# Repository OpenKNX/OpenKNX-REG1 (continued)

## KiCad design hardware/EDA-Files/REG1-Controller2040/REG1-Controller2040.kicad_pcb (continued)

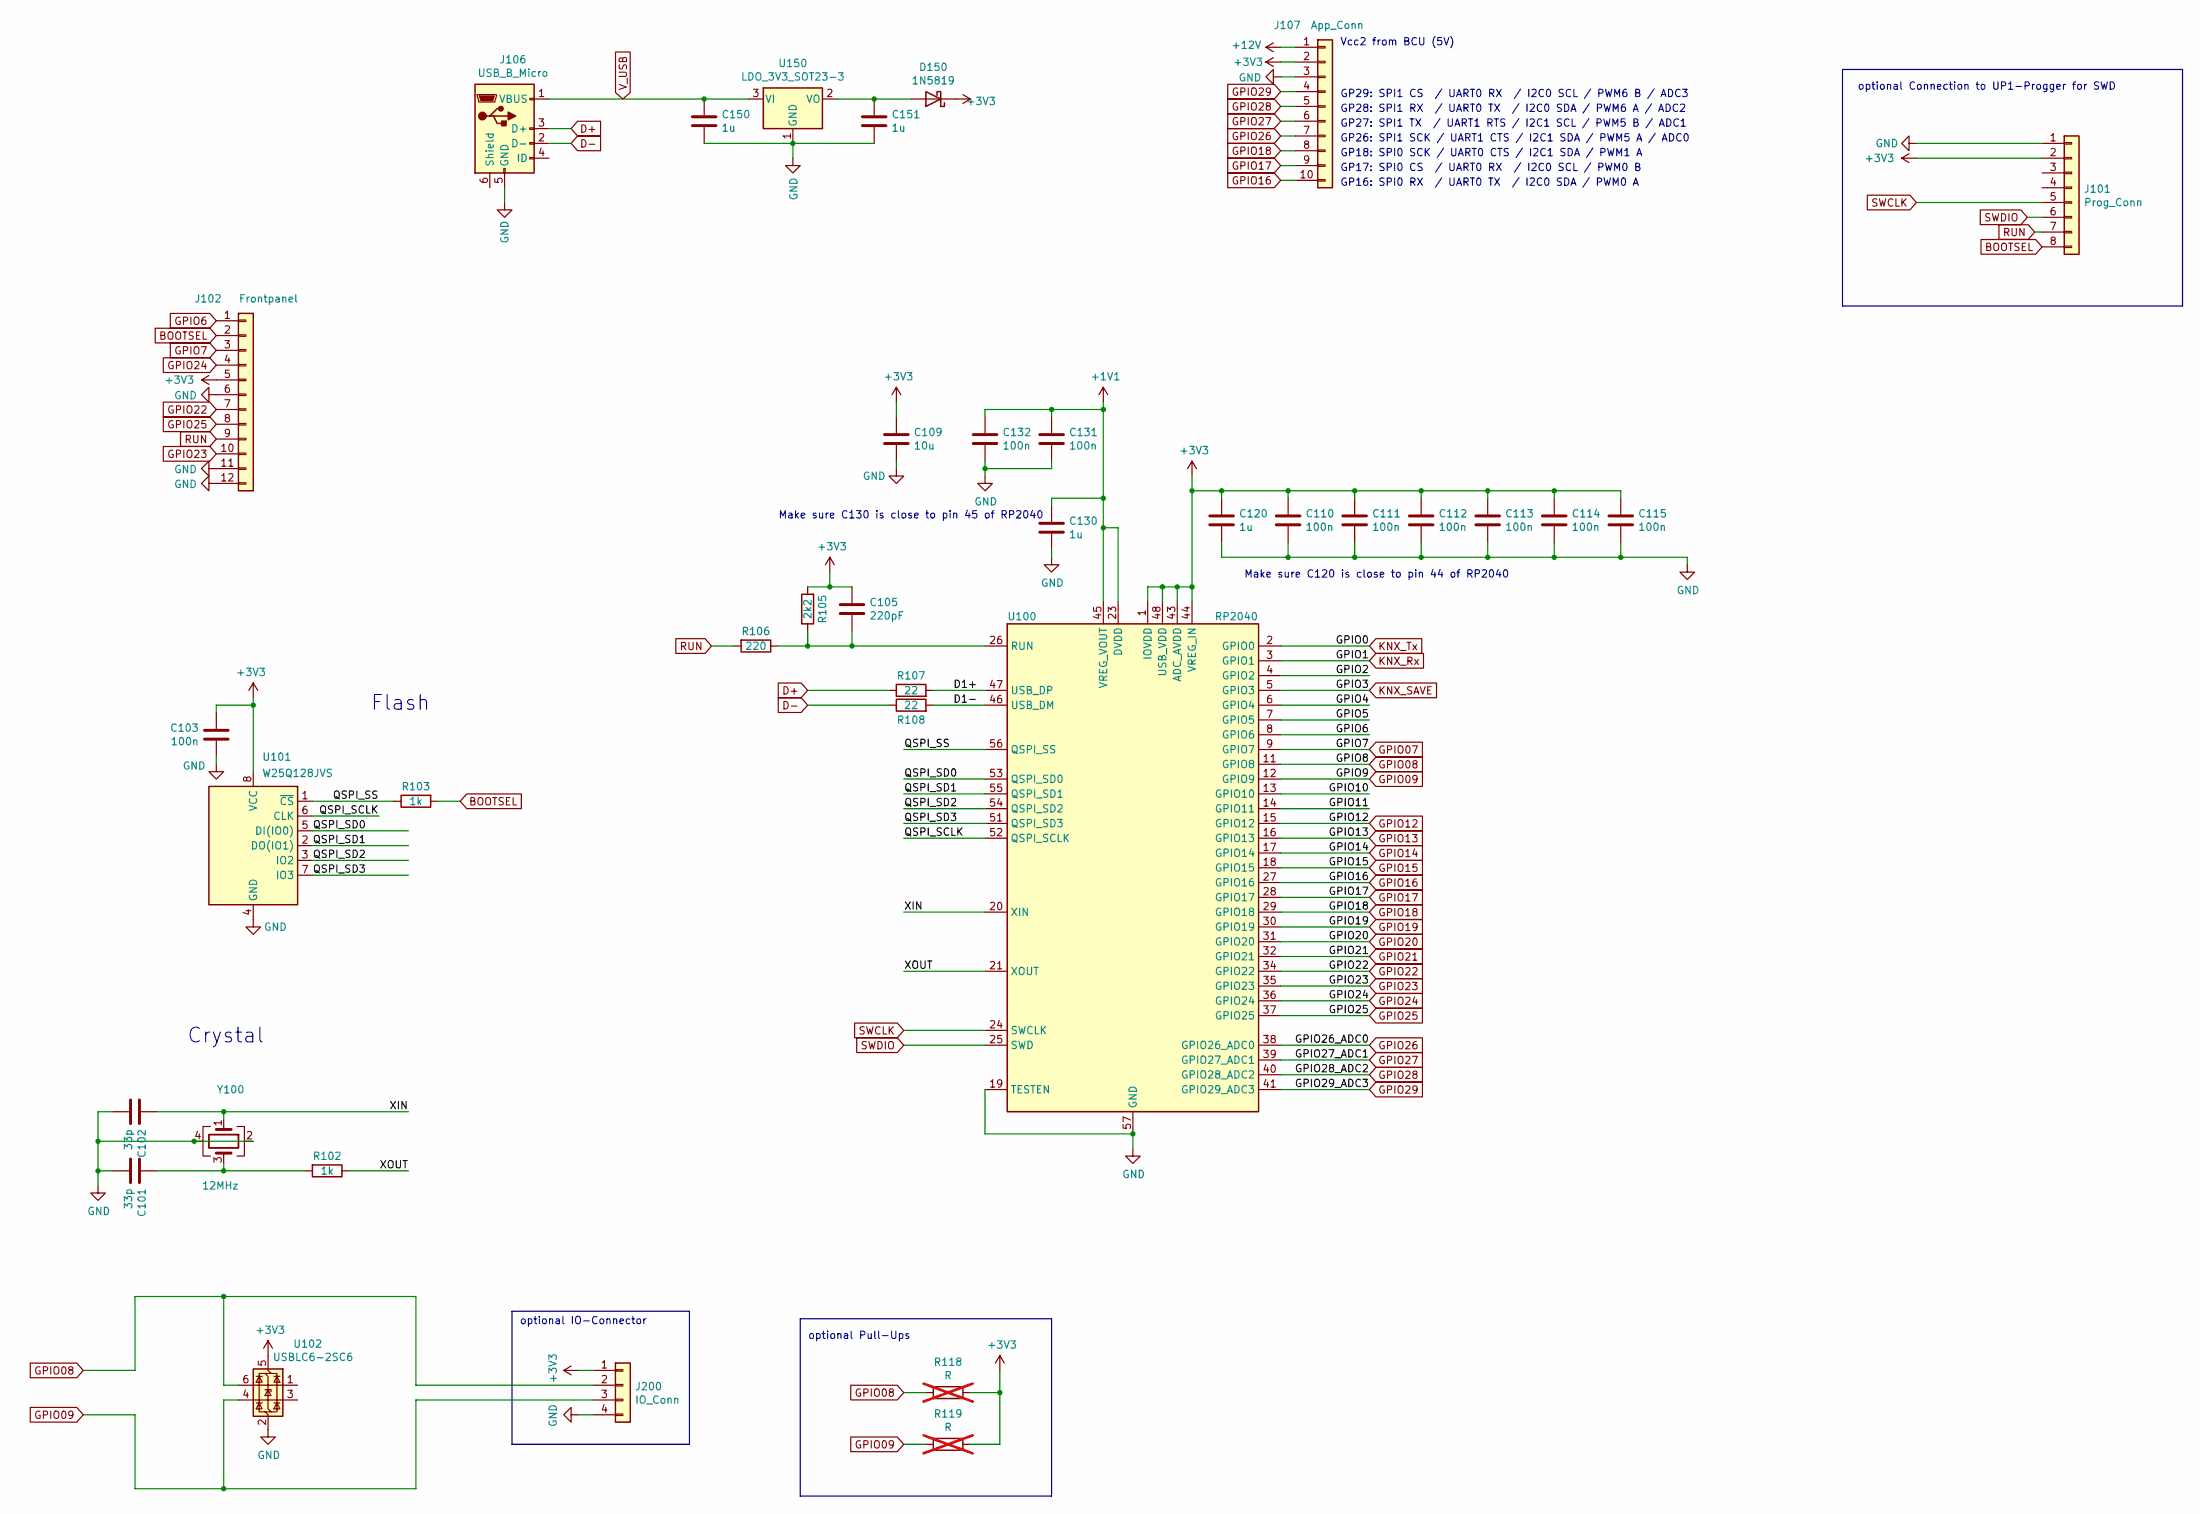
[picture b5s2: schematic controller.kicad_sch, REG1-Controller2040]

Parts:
C101, C102: 33p; C_0402_1005Metric
C103, C110, C111, C112, C113, C114, C115, C131, C132: 100n; C_0402_1005Metric
C105: 220pF; C_0402_1005Metric
C109: 10u; C_0805_2012Metric
C120, C130, C150, C151: 1u; C_0402_1005Metric
D150: 1N5819; D_SOD-323
J101: Prog_Conn; CONN-TH_1.25-8AW_reversed
J102: Frontpanel; CONN-TH-10P_AFC11-S10ICC-00
J106: USB_B_Micro; USB_Micro-B_JING_C10418
J107: App_Conn; PinHeader_1x10_P2.54mm_Vertical
J200: IO_Conn; PhoenixContact_MC_1,5_4-G-3.5_1x04_P3.50mm_Horizontal
R102, R103: 1k; R_0402_1005Metric
R105: 2k2; R_0402_1005Metric
R106: 220; R_0402_1005Metric
R107, R108: 22; R_0402_1005Metric
R118, R119: R; R_0805_2012Metric_Pad1.20x1.40mm_HandSolder; not fitted
U100: RP2040; RP2040-QFN-56_noThermalVias
U101: W25Q128JVS; SOIC-8_5.23x5.23mm_P1.27mm
U102: USBLC6-2SC6; SOT-23-6
U150: LDO_3V3_SOT23-3; SOT-23
Y100: 12MHz; Crystal_SMD_3225-4Pin_3.2x2.5mm

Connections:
+1V1: C130.1, C131.1, C132.1, U100.23 (DVDD), U100.45 (VREG_VOUT), U100.50 (DVDD)
+3V3: C103.1, C105.1, C109.1, C110.1, C111.1, C112.1, C113.1, C114.1, C115.1, C120.1, D150.1 (K), J101.2, J107.2, J200.1, R105.2, R118.1, R119.1, U100.1 (IOVDD), U100.10 (IOVDD), U100.22 (IOVDD), U100.33 (IOVDD), U100.42 (IOVDD), U100.43 (ADC_AVDD), U100.44 (VREG_IN), U100.48 (USB_VDD), U100.49 (IOVDD), U101.8 (VCC), U102.5 (VBUS); also elsewhere on the board
+12V: J107.1; also elsewhere on the board
/Controller/D1+: R107.2, U100.47 (USB_DP)
/Controller/D1-: R108.2, U100.46 (USB_DM)
/Controller/GPIO2: U100.4 (GPIO2)
/Controller/GPIO4: U100.6 (GPIO4)
/Controller/GPIO5: U100.7 (GPIO5)
/Controller/GPIO10: U100.13 (GPIO10)
/Controller/GPIO11: U100.14 (GPIO11)
/Controller/QSPI_SCLK: U100.52 (QSPI_SCLK), U101.6 (CLK)
/Controller/QSPI_SD0: U100.53 (QSPI_SD0), U101.5 (DI(IO0))
/Controller/QSPI_SD1: U100.55 (QSPI_SD1), U101.2 (DO(IO1))
/Controller/QSPI_SD2: U100.54 (QSPI_SD2), U101.3 (IO2)
/Controller/QSPI_SD3: U100.51 (QSPI_SD3), U101.7 (IO3)
/Controller/QSPI_SS: R103.1, U100.56 (QSPI_SS), U101.1 (~CS)
/Controller/XIN: C102.1, U100.20 (XIN), Y100.1
/Controller/XOUT: R102.1, U100.21 (XOUT)
BOOTSEL: J101.8, R103.2; also elsewhere on the board
D+: J106.3 (D+), R107.1
D-: J106.2 (D-), R108.1
GND: C101.2, C102.2, C103.2, C109.2, C110.2, C111.2, C112.2, C113.2, C114.2, C115.2, C120.2, C130.2, C131.2, C132.2, C150.2, C151.2, J101.1, J106.5 (GND), J107.3, J200.4, U100.19 (TESTEN), U100.57 (GND), U101.4 (GND), U102.2 (GND), U150.1 (GND), Y100.2, Y100.4; also elsewhere on the board
GPIO6: U100.8 (GPIO6); also elsewhere on the board
GPIO07: U100.9 (GPIO7); also elsewhere on the board
GPIO08: J200.2, R118.2, U100.11 (GPIO8), U102.6 (I/O1)
GPIO09: J200.3, R119.2, U100.12 (GPIO9), U102.4 (I/O2)
GPIO12: U100.15 (GPIO12)
GPIO13: U100.16 (GPIO13)
GPIO14: U100.17 (GPIO14)
GPIO15: U100.18 (GPIO15)
GPIO16: J107.10, U100.27 (GPIO16)
GPIO17: J107.9, U100.28 (GPIO17)
GPIO18: J107.8, U100.29 (GPIO18)
GPIO19: U100.30 (GPIO19)
GPIO20: U100.31 (GPIO20)
GPIO21: U100.32 (GPIO21)
GPIO22: U100.34 (GPIO22); also elsewhere on the board
GPIO23: U100.35 (GPIO23); also elsewhere on the board
GPIO24: U100.36 (GPIO24); also elsewhere on the board
GPIO25: U100.37 (GPIO25); also elsewhere on the board
GPIO26: J107.7, U100.38 (GPIO26_ADC0)
GPIO27: J107.6, U100.39 (GPIO27_ADC1)
GPIO28: J107.5, U100.40 (GPIO28_ADC2)
GPIO29: J107.4, U100.41 (GPIO29_ADC3)
KNX_Rx: U100.3 (GPIO1); also elsewhere on the board
KNX_SAVE: U100.5 (GPIO3); also elsewhere on the board
KNX_Tx: U100.2 (GPIO0); also elsewhere on the board
unnamed: C101.1, R102.2, Y100.3
unnamed: C151.1, D150.2 (A), U150.2 (VO)
unnamed: C105.2, R105.1, R106.1, U100.26 (RUN)
RUN: J101.7, R106.2; also elsewhere on the board
SWCLK: J101.5, U100.24 (SWCLK)
SWDIO: J101.6, U100.25 (SWD)
V_USB: C150.1, J106.1 (VBUS), U150.3 (VI)

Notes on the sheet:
GP18: SPI0 SCK / UART0 CTS / I2C1 SDA / PWM1 A
GP16: SPI0 RX / UART0 TX / I2C0 SDA / PWM0 A
optional Connection to UP1-Progger for SWD
Make sure C130 is close to pin 45 of RP2040
GP17: SPI0 CS / UART0 RX / I2C0 SCL / PWM0 B
Vcc2 from BCU (5V)
GP29: SPI1 CS / UART0 RX / I2C0 SCL / PWM6 B / ADC3
Flash
GP28: SPI1 RX / UART0 TX / I2C0 SDA / PWM6 A / ADC2
GP26: SPI1 SCK / UART1 CTS / I2C1 SDA / PWM5 A / ADC0
optional Pull-Ups
Crystal
GP27: SPI1 TX / UART1 RTS / I2C1 SCL / PWM5 B / ADC1
optional IO-Connector
Make sure C120 is close to pin 44 of RP2040

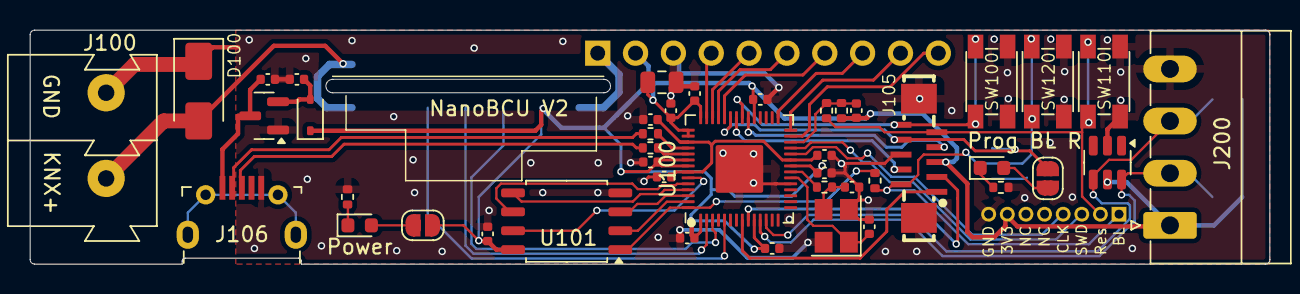
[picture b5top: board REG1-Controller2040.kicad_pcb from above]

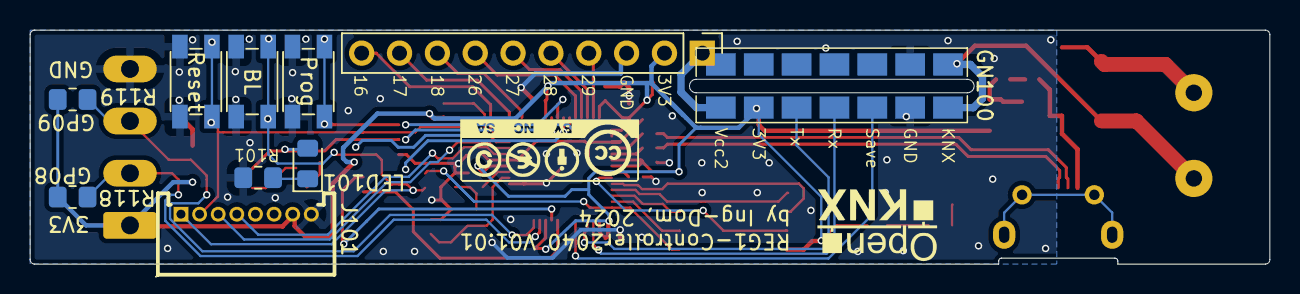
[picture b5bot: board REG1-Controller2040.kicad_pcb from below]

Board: 2 copper layers, 83.2 x 15.7 mm, 55 parts (12 on the bottom side), 48 nets.

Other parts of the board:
G1: LOGO; CC-BY-NY-SA_12x4
G2: LOGO; OpenKNX_Logo_10x10
J105: Frontpanel; CONN-TH-10P_AFC11-S10ICC-00

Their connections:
+3V3: J105.5; also elsewhere on the board
BOOTSEL: J105.2; also elsewhere on the board
GND: J105.6, J105.11, J105.12; also elsewhere on the board
GPIO6: J105.1; also elsewhere on the board
GPIO07: J105.3; also elsewhere on the board
GPIO22: J105.7; also elsewhere on the board
GPIO23: J105.10; also elsewhere on the board
GPIO24: J105.4; also elsewhere on the board
GPIO25: J105.8; also elsewhere on the board
RUN: J105.9; also elsewhere on the board

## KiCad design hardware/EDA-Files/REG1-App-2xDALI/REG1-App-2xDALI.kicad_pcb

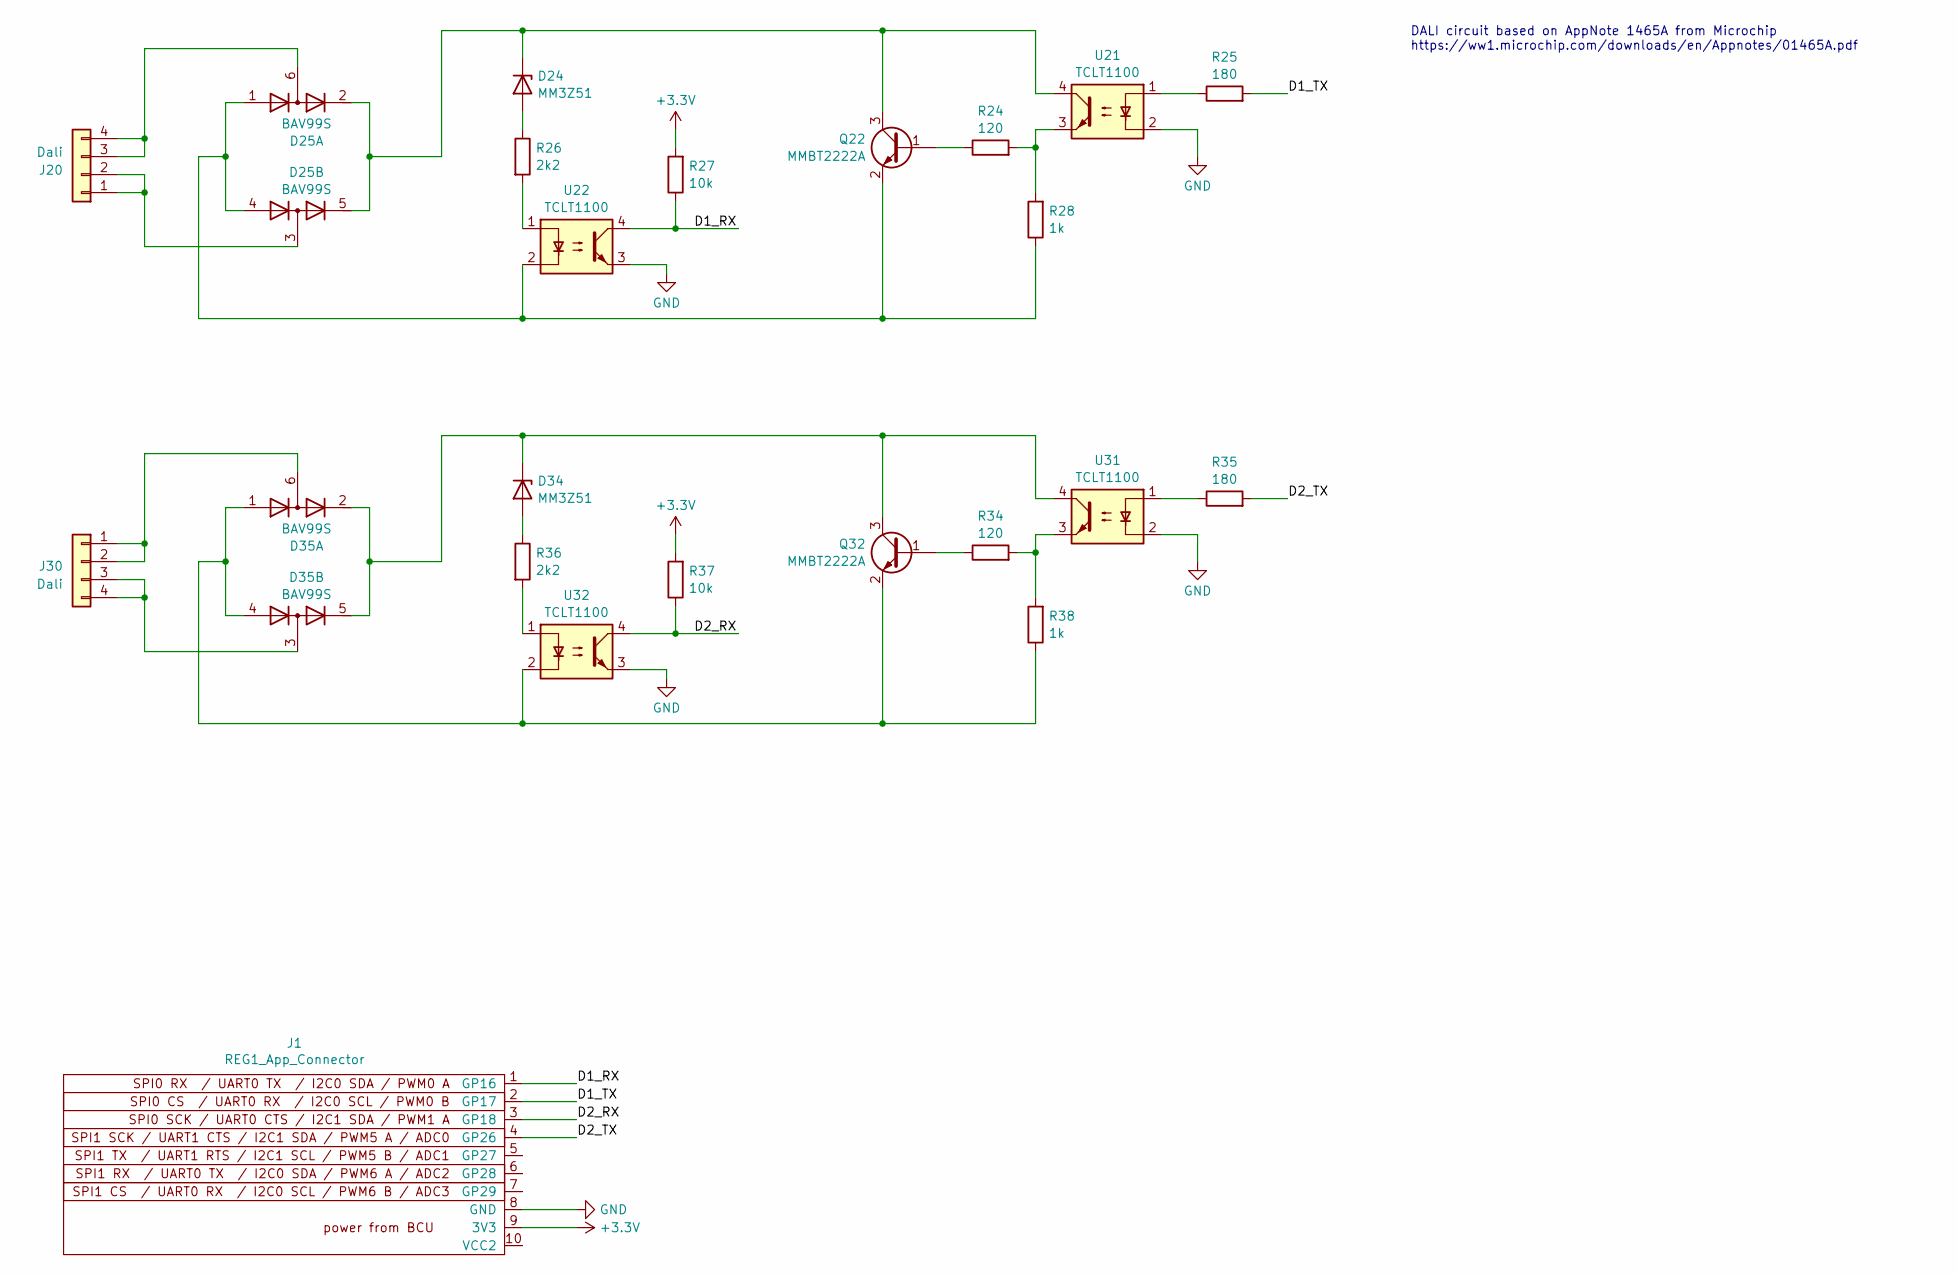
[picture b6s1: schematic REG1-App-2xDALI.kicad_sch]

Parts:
D24, D34: MM3Z51; D_SOD-323F
D25, D35: BAV99S; SOT-363_SC-70-6
J1: REG1_App_Connector; PinHeader_1x10_P2.54mm_Horizontal
J20, J30: Dali; PhoenixContact_MC_1,5_4-G-3.5_1x04_P3.50mm_Horizontal
Q22, Q32: MMBT2222A; SOT-23
R24, R34: 120; R_0603_1608Metric
R25, R35: 180; R_0603_1608Metric
R26, R36: 2k2; R_0603_1608Metric
R27, R37: 10k; R_0603_1608Metric
R28, R38: 1k; R_0603_1608Metric
U21, U22, U31, U32: TCLT1100; SOP-4_7.5x4.1mm_P2.54mm

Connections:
+3.3V: J1.9 (3V3), R27.2, R37.2
/D1_RX: J1.1 (GP16), R27.1, U22.4
/D1_TX: J1.2 (GP17), R25.2
/D2_RX: J1.3 (GP18), R37.1, U32.4
/D2_TX: J1.4 (GP26), R35.2
GND: J1.8 (GND), U21.2, U22.3, U31.2, U32.3
unnamed: D24.2 (A), R26.1
unnamed: D24.1 (K), D25.2 (K2), D25.5 (K4), Q22.3 (C), U21.4
unnamed: D25.1 (A1), D25.4 (A3), Q22.2 (E), R28.1, U22.2
unnamed: D25.6 (K3A4), J20.3, J20.4
unnamed: D25.3 (K1A2), J20.1, J20.2
unnamed: D34.2 (A), R36.1
unnamed: D34.1 (K), D35.2 (K2), D35.5 (K4), Q32.3 (C), U31.4
unnamed: D35.1 (A1), D35.4 (A3), Q32.2 (E), R38.1, U32.2
unnamed: D35.6 (K3A4), J30.1, J30.2
unnamed: D35.3 (K1A2), J30.3, J30.4
unnamed: Q22.1 (B), R24.1
unnamed: Q32.1 (B), R34.1
unnamed: R24.2, R28.2, U21.3
unnamed: R25.1, U21.1
unnamed: R26.2, U22.1
unnamed: R34.2, R38.2, U31.3
unnamed: R35.1, U31.1
unnamed: R36.2, U32.1

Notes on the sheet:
DALI circuit based on AppNote 1465A from Microchip https://ww1.microchip.com/downloads/en/Appnotes/01465A.pdf

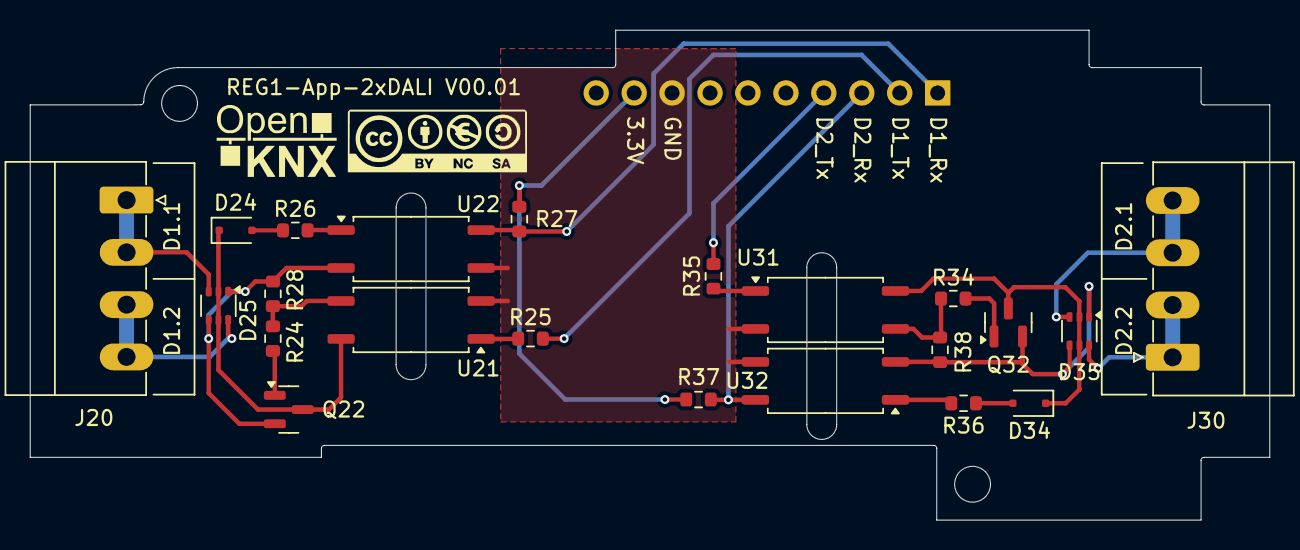
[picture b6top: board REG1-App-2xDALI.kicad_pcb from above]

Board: 2 copper layers, 83.0 x 32.8 mm, 25 parts (1 on the bottom side), 24 nets.

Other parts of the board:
G1: LOGO; CC-BY-NY-SA_12x4
G2: LOGO; OpenKNX_Logo_10x10

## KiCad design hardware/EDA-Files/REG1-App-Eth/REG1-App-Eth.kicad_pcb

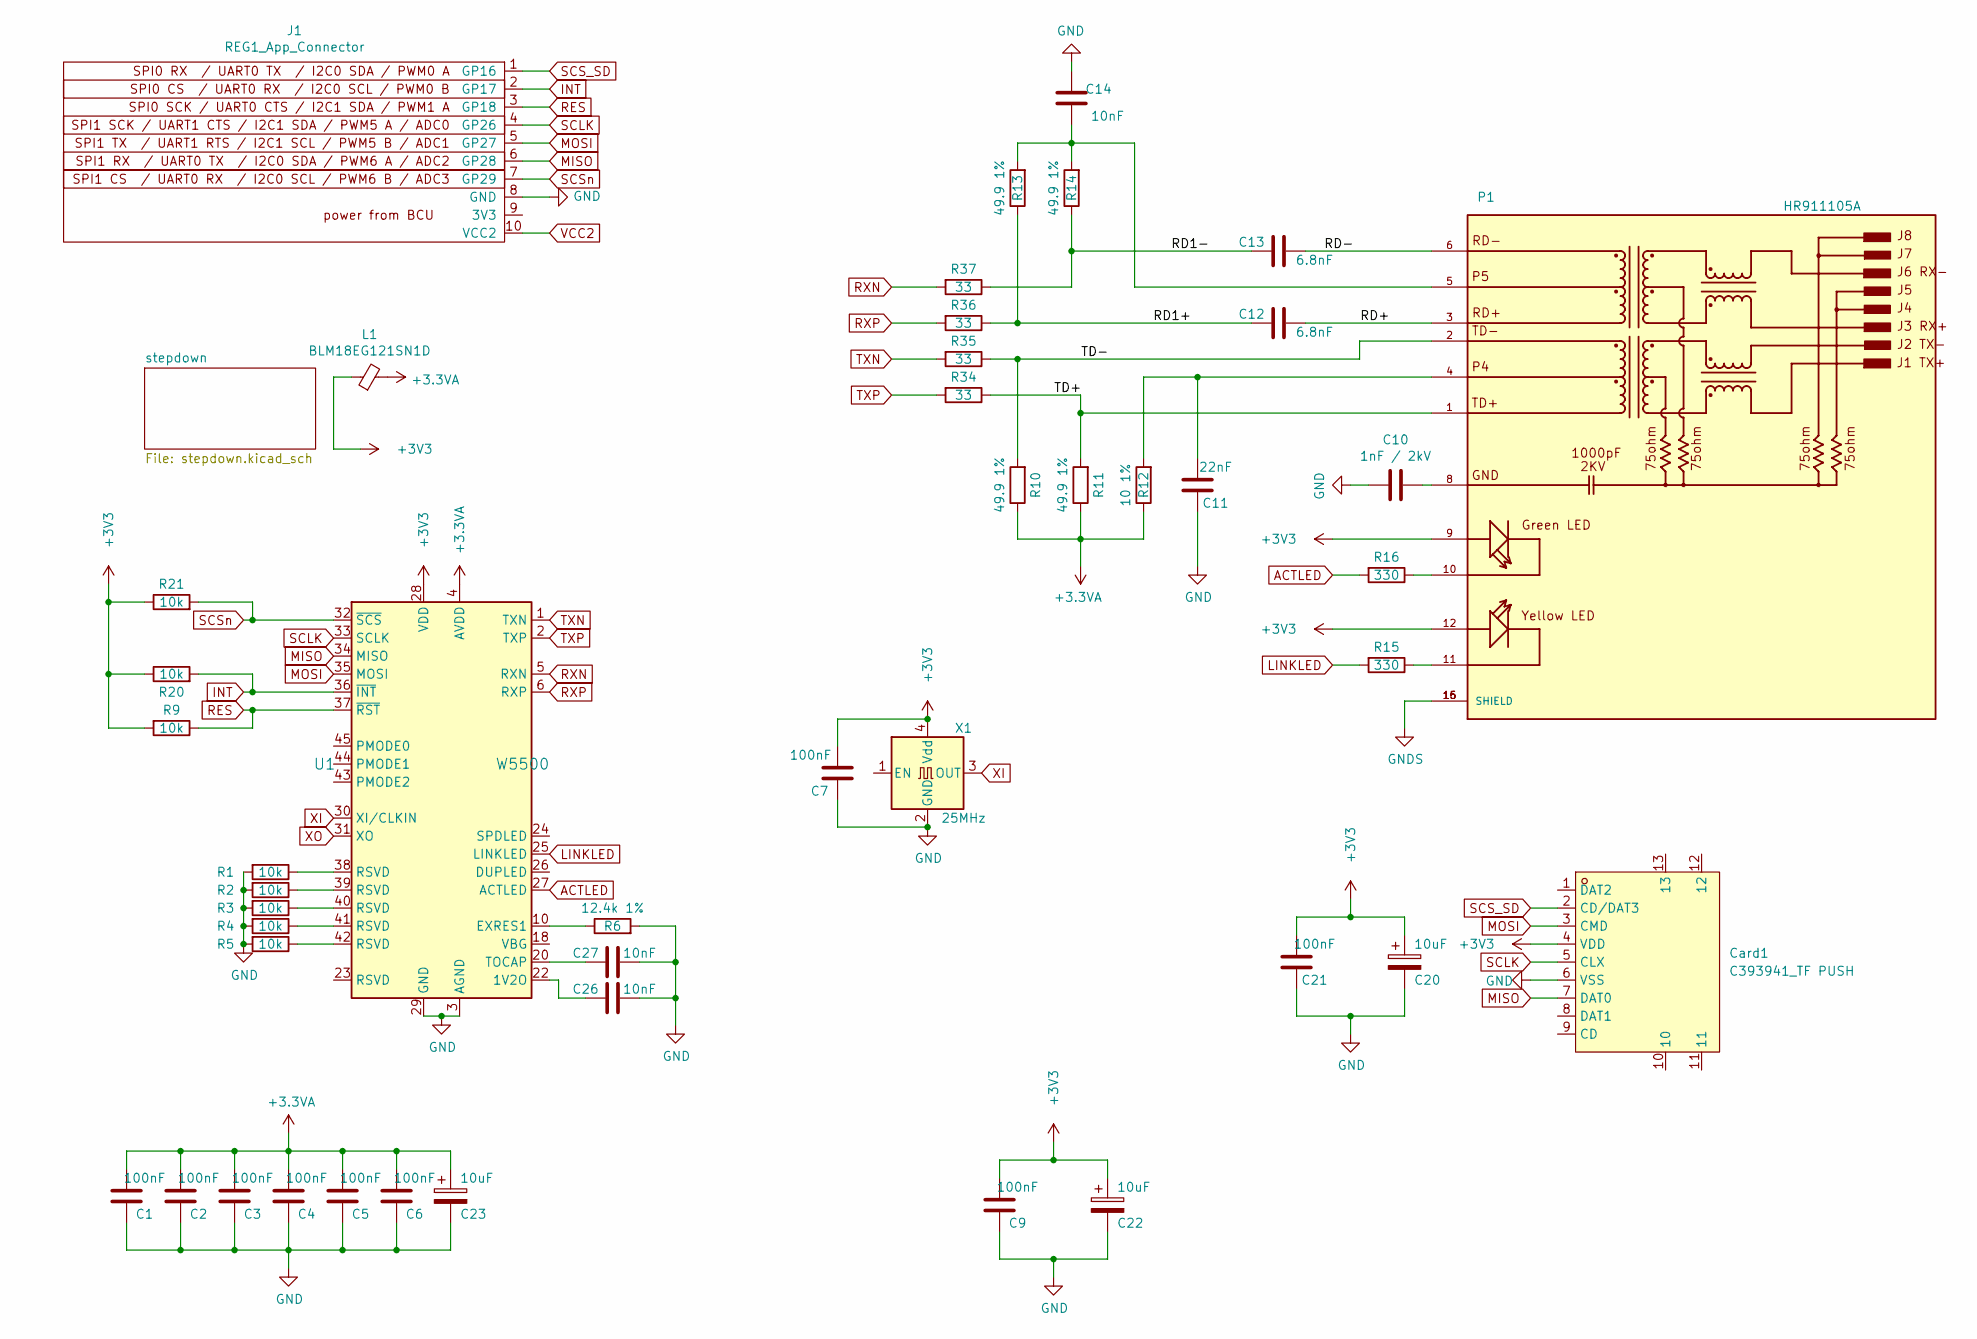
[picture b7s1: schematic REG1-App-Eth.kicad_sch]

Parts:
C1, C2, C3, C4, C5, C6, C7, C9, C21: 100nF; C_0402_1005Metric
C10: 1nF / 2kV; C_1206_3216Metric
C11: 22nF; C_0402_1005Metric
C12, C13: 6.8nF; C_0402_1005Metric
C14, C26, C27: 10nF; C_0402_1005Metric
C20, C22, C23: 10uF; CP_EIA-3216-18_Kemet-A
Card1: C393941_TF PUSH; C393941_TF-SMD_TF-PUSH_Handsolder
J1: REG1_App_Connector; PinHeader_1x10_P2.54mm_Horizontal
L1: BLM18EG121SN1D; L_0603_1608Metric
P1: HR911105A; HANRUN_HR911105A; PARTREV A
R1, R2, R3, R4, R5, R9, R20, R21: 10k; R_0402_1005Metric
R6: 12.4k 1%; R_0402_1005Metric
R10, R11, R13, R14: 49.9 1%; R_0402_1005Metric
R12: 10 1%; R_0402_1005Metric
R15, R16: 330; R_0402_1005Metric
R34, R35, R36, R37: 33; R_0402_1005Metric
U1: W5500; LQFP-48_7x7mm_P0.5mm; MPN W5500; Digi-Key_PN 1278-1021-ND
X1: 25MHz; Crystal_SMD_3225-4Pin_3.2x2.5mm

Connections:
+3.3VA: C1.1, C2.1, C3.1, C4.1, C5.1, C6.1, C23.1, L1.2, R10.1, R11.1, R12.1, U1.4 (AVDD), U1.8 (AVDD), U1.11 (AVDD), U1.15 (AVDD), U1.17 (AVDD), U1.21 (AVDD)
+3V3: C7.1, C9.1, C20.1, C21.1, C22.1, Card1.4 (VDD), L1.1, P1.9, P1.12, R9.2, R20.1, R21.1, U1.28 (VDD), X1.4 (Vdd); also elsewhere on the board
/RD1+: C12.2, R13.1, R36.1
/RD1-: C13.2, R14.1, R37.1
/RD+: C12.1, P1.3
/RD-: C13.1, P1.6
/TD+: P1.1, R11.2, R34.1
/TD-: P1.2, R10.2, R35.1
ACTLED: R16.2, U1.27 (ACTLED)
GND: C1.2, C2.2, C3.2, C4.2, C5.2, C6.2, C7.2, C9.2, C10.2, C11.2, C14.2, C20.2, C21.2, C22.2, C23.2, C26.1, C27.2, Card1.6 (VSS), J1.8 (GND), R1.2, R2.2, R3.2, R4.2, R5.2, R6.2, U1.3 (AGND), U1.9 (AGND), U1.14 (AGND), U1.16 (AGND), U1.19 (AGND), U1.29 (GND), U1.48 (AGND), X1.2 (GND); also elsewhere on the board
GNDS: P1.15 (SHIELD), P1.16 (SHIELD)
INT: J1.2 (GP17), R20.2, U1.36 (~INT)
LINKLED: R15.2, U1.25 (LINKLED)
MISO: Card1.7 (DAT0), J1.6 (GP28), U1.34 (MISO)
MOSI: Card1.3 (CMD), J1.5 (GP27), U1.35 (MOSI)
unnamed: C10.1, P1.8
unnamed: C11.1, P1.4, R12.2
unnamed: C14.1, P1.5, R13.2, R14.2
unnamed: P1.10, R16.1
unnamed: P1.11, R15.1
unnamed: R1.1, U1.38 (RSVD)
unnamed: R2.1, U1.39 (RSVD)
unnamed: R3.1, U1.40 (RSVD)
unnamed: R4.1, U1.41 (RSVD)
unnamed: R5.1, U1.42 (RSVD)
unnamed: C26.2, U1.22 (1V2O)
unnamed: R6.1, U1.10 (EXRES1)
unnamed: C27.1, U1.20 (TOCAP)
RES: J1.3 (GP18), R9.1, U1.37 (~RST)
RXN: R37.2, U1.5 (RXN)
RXP: R36.2, U1.6 (RXP)
SCLK: Card1.5 (CLX), J1.4 (GP26), U1.33 (SCLK)
SCS_SD: Card1.2 (CD/DAT3), J1.1 (GP16)
SCSn: J1.7 (GP29), R21.2, U1.32 (~SCS)
TXN: R35.2, U1.1 (TXN)
TXP: R34.2, U1.2 (TXP)
VCC2: J1.10 (VCC2); also elsewhere on the board
XI: U1.30 (XI/CLKIN), X1.3 (OUT)
XO: U1.31 (XO)

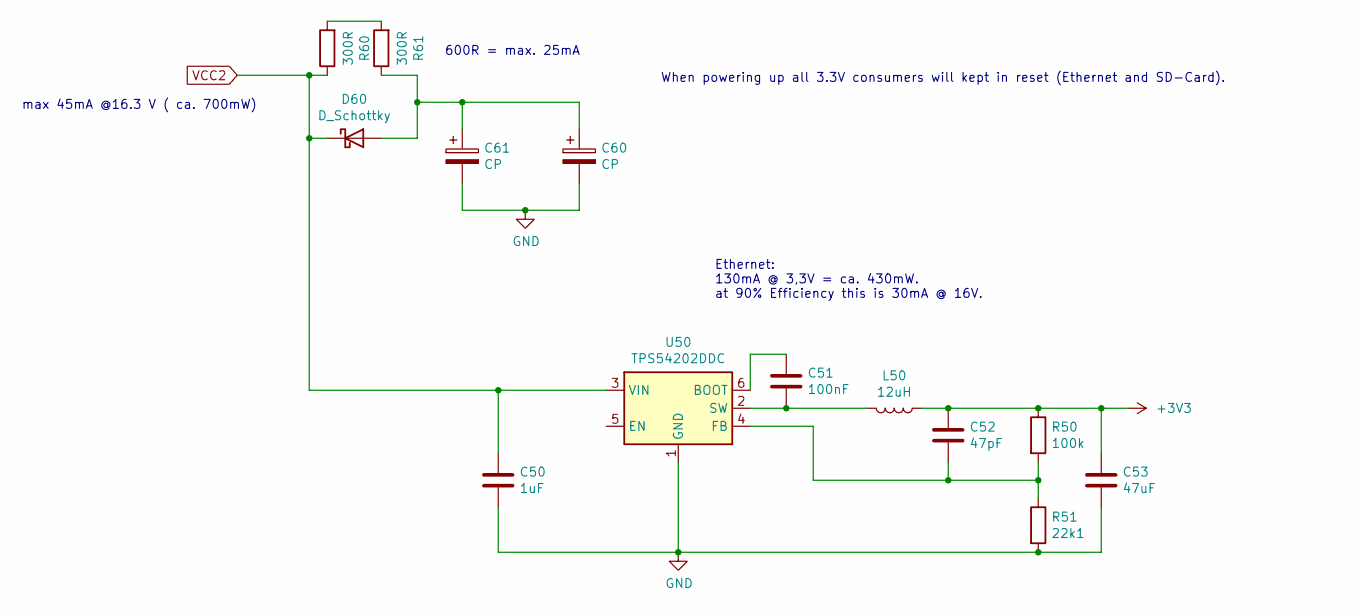
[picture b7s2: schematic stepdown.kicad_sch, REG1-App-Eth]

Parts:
C50: 1uF; C_0805_2012Metric
C51: 100nF; C_0603_1608Metric
C52: 47pF; C_0603_1608Metric
C53: 47uF; C_1206_3216Metric
C60, C61: CP; CP_Radial_D10.0mm_H20.0mm_P5.00mm_Horizontal
D60: D_Schottky; D_SOD-323
L50: 12uH; C96886_IND-SMD_L4.0-W4.0_Handsolder
R50: 100k; R_0603_1608Metric
R51: 22k1; R_0603_1608Metric
R60, R61: 300R; R_1206_3216Metric
U50: TPS54202DDC; SOT-23-6_Handsoldering

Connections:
+3V3: C52.1, C53.1, L50.1, R50.1; also elsewhere on the board
GND: C50.2, C53.2, C60.2, C61.2, R51.2, U50.1 (GND); also elsewhere on the board
unnamed: C60.1, C61.1, D60.2 (A), R61.1
unnamed: R60.2, R61.2
unnamed: C51.1, U50.6 (BOOT)
unnamed: C52.2, R50.2, R51.1, U50.4 (FB)
unnamed: C51.2, L50.2, U50.2 (SW)
VCC2: C50.1, D60.1 (K), R60.1, U50.3 (VIN); also elsewhere on the board

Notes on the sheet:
max 45mA @16.3 V ( ca. 700mW)
Ethernet: 130mA @ 3,3V = ca. 430mW. at 90% Efficiency this is 30mA @ 16V.
When powering up all 3.3V consumers will kept in reset (Ethernet and SD-Card).
600R = max. 25mA

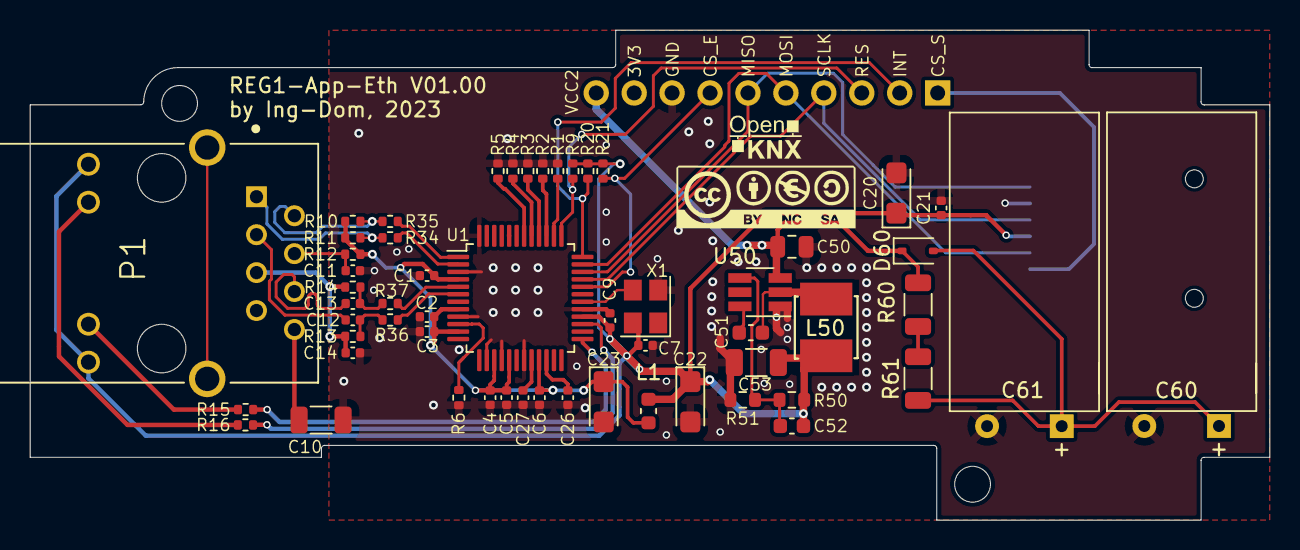
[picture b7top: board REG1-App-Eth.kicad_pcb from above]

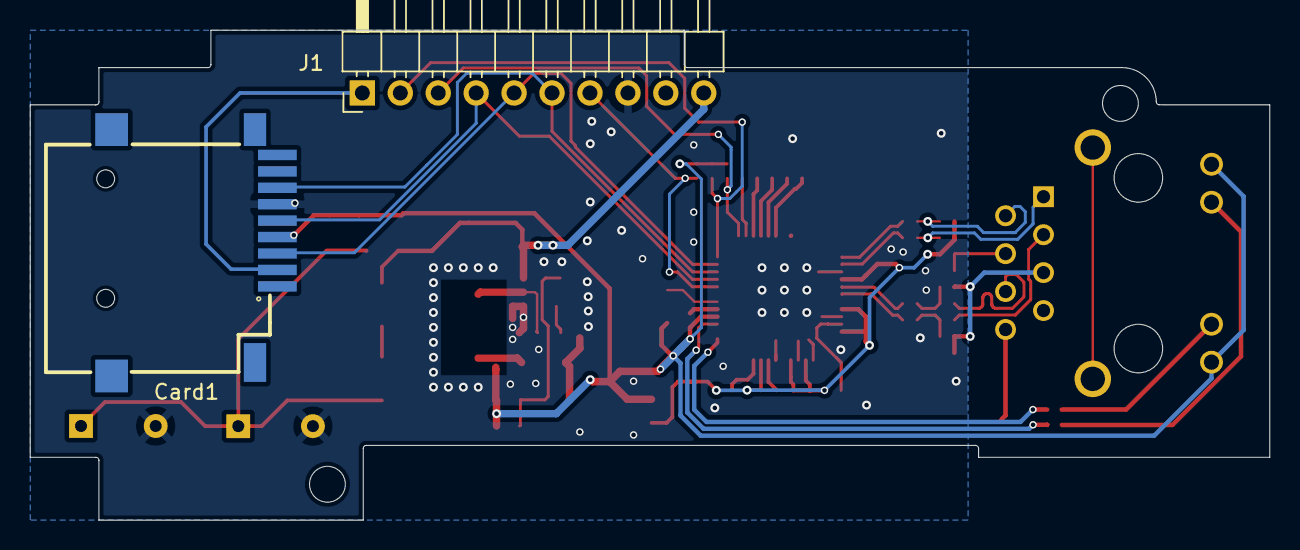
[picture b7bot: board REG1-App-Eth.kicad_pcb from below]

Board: 2 copper layers, 83.0 x 32.8 mm, 60 parts (2 on the bottom side), 43 nets.

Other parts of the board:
G1: LOGO; CC-BY-NY-SA_12x4
G2: LOGO; OpenKNX_Logo_6x6

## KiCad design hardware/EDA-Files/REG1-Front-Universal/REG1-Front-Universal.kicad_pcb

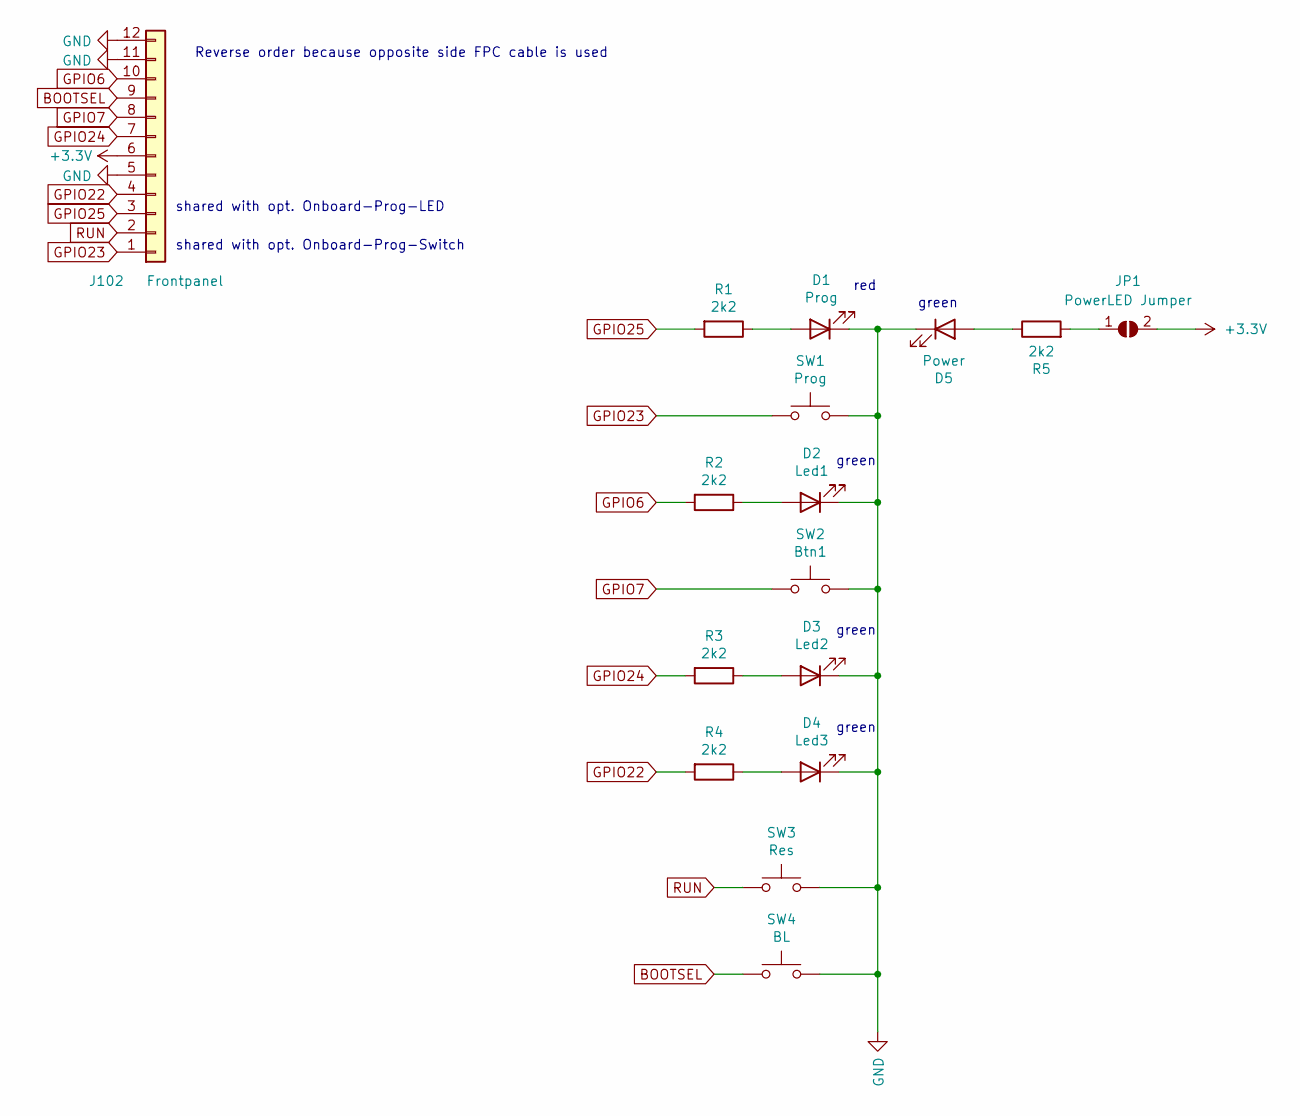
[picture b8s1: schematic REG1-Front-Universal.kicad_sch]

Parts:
D1: Prog; LED_0603_1608Metric
D2: Led1; LED_0603_1608Metric
D3: Led2; LED_0603_1608Metric
D4: Led3; LED_0603_1608Metric
D5: Power; LED_0603_1608Metric
J102: Frontpanel; C11050_FPC-SMD_P0.5-10P_LSXJ-H2.0-10P
JP1: PowerLED Jumper; SolderJumper-2_P1.3mm_Open_RoundedPad1.0x1.5mm
R1, R2, R3, R4, R5: 2k2; R_0402_1005Metric
SW1: Prog; C455282_SW-SMD_4P-L4.2-W3.3-P2.15-LS5.1
SW2: Btn1; C455282_SW-SMD_4P-L4.2-W3.3-P2.15-LS5.1
SW3: Res; C455282_SW-SMD_4P-L4.2-W3.3-P2.15-LS5.1
SW4: BL; C455282_SW-SMD_4P-L4.2-W3.3-P2.15-LS5.1

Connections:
+3.3V: JP1.2 (B); also elsewhere on the board
BOOTSEL: SW4.1; also elsewhere on the board
GND: D1.1 (K), D2.1 (K), D3.1 (K), D4.1 (K), D5.1 (K), SW1.2, SW2.2, SW3.2, SW4.2; also elsewhere on the board
GPIO6: R2.2; also elsewhere on the board
GPIO7: SW2.1; also elsewhere on the board
GPIO22: R4.2; also elsewhere on the board
GPIO23: SW1.1; also elsewhere on the board
GPIO24: R3.2; also elsewhere on the board
GPIO25: R1.2; also elsewhere on the board
unnamed: D1.2 (A), R1.1
unnamed: D2.2 (A), R2.1
unnamed: D3.2 (A), R3.1
unnamed: D4.2 (A), R4.1
unnamed: D5.2 (A), R5.1
unnamed: JP1.1 (A), R5.2
RUN: SW3.1; also elsewhere on the board

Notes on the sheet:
green
red
Reverse order because opposite side FPC cable is used
shared with opt. Onboard-Prog-Switch
shared with opt. Onboard-Prog-LED

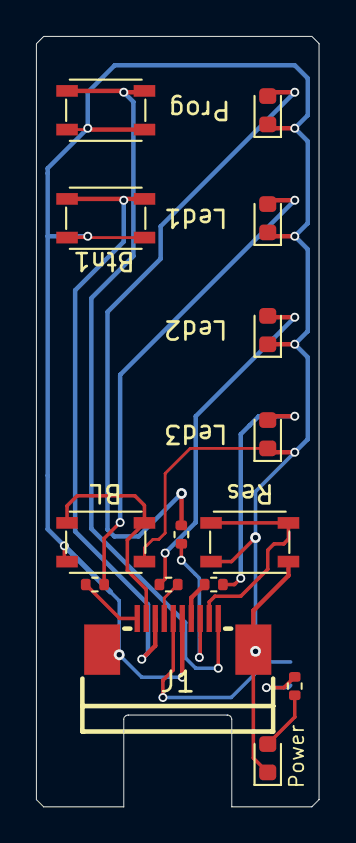
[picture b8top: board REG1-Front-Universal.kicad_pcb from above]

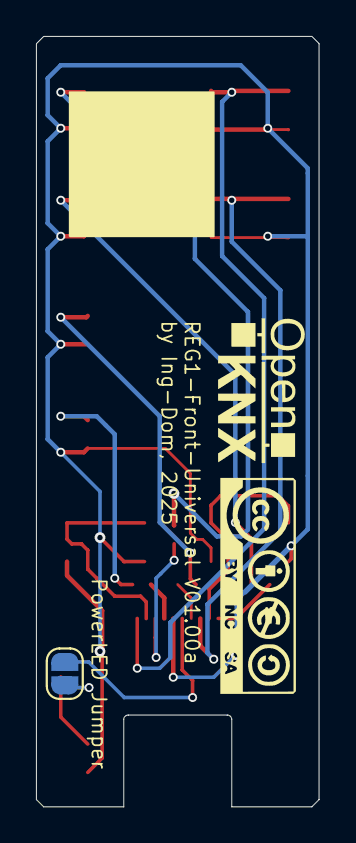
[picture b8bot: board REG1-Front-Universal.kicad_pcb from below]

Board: 2 copper layers, 15.7 x 42.8 mm, 18 parts (3 on the bottom side), 16 nets.

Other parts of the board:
G1: LOGO; OpenKNX_Logo_10x10
G2: LOGO; CC-BY-NY-SA_12x4
J1: Frontpanel; C11050_FPC-SMD_P0.5-10P_LSXJ-H2.0-10P

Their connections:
+3.3V: J1.6; also elsewhere on the board
BOOTSEL: J1.9; also elsewhere on the board
GND: J1.5, J1.11, J1.12; also elsewhere on the board
GPIO6: J1.10; also elsewhere on the board
GPIO7: J1.8; also elsewhere on the board
GPIO22: J1.4; also elsewhere on the board
GPIO23: J1.1; also elsewhere on the board
GPIO24: J1.7; also elsewhere on the board
GPIO25: J1.3; also elsewhere on the board
RUN: J1.2; also elsewhere on the board

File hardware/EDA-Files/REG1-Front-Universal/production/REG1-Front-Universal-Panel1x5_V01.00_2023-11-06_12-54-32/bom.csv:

Designator,Footprint,Quantity,Value,LCSC Part #
"D1_5, D1_4, D1_3, D1_2, D1",0603,5,Prog,C2286
"D2_5, D2_4, D2_3, D2_2, D2",0603,5,Led1,C72043
"D3_5, D3_4, D3_3, D3_2, D3",0603,5,Led2,C72043
"D4_5, D4_4, D4_3, D4_2, D4",0603,5,Led3,C72043
"D5_5, D5_4, D5_3, D5_2, D5",0603,5,Power,C72043
"J1_5, J1_4, J1_3, J1_2, J1",C11050_FPC-SMD_P0.5-10P_LSXJ-H2.0-10P,5,Frontpanel,C11050
"R1_5, R1_4, R1_3, R1_2, R1, R2_5, R2_4, R2_3, R2_2, R2, R3_5, R3_4, R3_3, R3_2, R3, R4_5, R4_4, R4_3, R4_2, R4, R5_5, R5_4, R5_3, R5_2, R5",0402,25,2k2,C25879
"SW1_5, SW1_4, SW1_3, SW1_2, SW1",C455282_SW-SMD_4P-L4.2-W3.3-P2.15-LS5.1,5,Prog,C455282
"SW2_5, SW2_4, SW2_3, SW2_2, SW2",C455282_SW-SMD_4P-L4.2-W3.3-P2.15-LS5.1,5,Btn1,C455282
"SW3_5, SW3_4, SW3_3, SW3_2, SW3",C455282_SW-SMD_4P-L4.2-W3.3-P2.15-LS5.1,5,Res,C455282
"SW4_5, SW4_4, SW4_3, SW4_2, SW4",C455282_SW-SMD_4P-L4.2-W3.3-P2.15-LS5.1,5,BL,C455282

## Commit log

2022-11-02 added prototype renderings
2022-11-02 added doc
2022-11-02 REG1-App-Universal V00.01 and REG1-Front-Universal V00.01
2022-11-04 rotate connector, rotate switches, 0.2mm smaller on each side, corrected pinout of connector
2022-11-05 Front V00.02
2022-11-05 REG1-Controller2040_V00.03
2022-11-05 REG1-App-Universal V00.02
2022-11-05 added missing drl files to App-Universal V00.02
2022-11-21 added pictures fo assembly
2022-11-21 added pic
2023-01-04 added Case stls REG1-Controller-Module-Case_V01.00 REG1-Case_V01.00
2023-01-05 added documentation
2023-01-05 added Controller2040 V00.10 renderings
2023-01-28 fixed schematic
2023-01-28 added red led
2023-01-28 added Panel
2023-01-31 editorial V00.10 of App-Universal
2023-04-14 ignore
2023-10-15 REG1-App-Universal V00.90
2023-10-15 REG1-App-Universal_V01.00
2023-10-15 gitignore
2023-10-18 added REG1-App-8xBE
2023-10-19 wip 8xBE
2023-10-19 rename
2023-11-06 REG1-Front-Universal V01.00
2023-11-08 rm prl
2023-11-13 increased size of Front-Universal, WIP
2023-11-13 new V01.00 (some 0.1 bigger)
2023-11-14 added Pictures for REG1 V1 devices
2023-12-09 added STLs for REG1-Case V1
2023-12-14 added schematics
2024-01-25 added App-Dali
2024-01-28 adding REG1-Dali pictures
2024-04-23 add wip for a dali power supply
2024-07-26 draft RF App
2024-07-28 wip GW RF
2024-07-29 App-GW-RF2G4 V00.01
2024-07-29 added docu
2024-08-03 GW RF2G4 V00.01
2024-08-05 remove draft for App-8xBE
2024-12-03 REG1-App-Universal - editorial rework V01.10
2024-12-03 REG1-Universal pics
2024-12-20 app eth done
2024-12-20 add IPController
2025-01-09 REG1-Front-Universal_V01.01
2025-01-09 completed schematics in doc
2025-02-02 add REG1-Dali V01.20 stuff
2025-02-02 REG1-App-2xDALI
2025-02-03 add REG1-SEN-Multi Pictures
2025-02-05 add REG1-Controller2040
2025-02-05 remove AGPL
2025-02-05 move CC License on level up
2025-02-07 add some REG1 ESP pictures
2025-05-02 update REG1-SEN-Multi_Label
2025-07-13 REG1 Case V01.20 STL compilation
2025-07-31 update REG1-Case-IP
2025-07-31 add pics
2025-08-14 REG1-SA-4xSELV
2025-11-26 add REG1-App-SEN-Multi
2026-04-14 NanoDCU V00.02
2026-04-14 REG1-Front-RGB V00.01
2026-04-21 add older REG1-ControllerESP schematics
2026-05-01 REG1-App-SEN-Multi V01.00 - editorial change to V01.00 after Beta
